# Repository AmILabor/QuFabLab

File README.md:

# QuFabLab

### Open Quantum Experiments for FabLabs and Education

QuFabLab is an open-source platform for building and exploring interactive quantum optics experiments using modular hardware, embedded systems, and augmented reality.

The project combines physical experiment components with real-time AR visualization, allowing students to build optical experiments while simultaneously observing the quantum behavior of the system.

QuFabLab aims to make quantum technologies accessible in FabLabs, universities, and STEM education environments.

---

# Project Overview

QuFabLab is centered around the AR Quantenkoffer (Quantum Suitcase) — a portable experimental platform that enables users to construct optical experiments using modular components.

The system automatically detects the configuration of the experiment and visualizes it using Microsoft HoloLens 2.

This enables a new form of learning where physical experimentation and digital visualization are combined.

---

# System Architecture

```id="g82x1a"
Experiment Bricks
      │
      │  I2C / GPIO
      ▼
Experiment Field
      │
      ▼
Raspberry Pi (QuCase Backend)
      │
      │ WebSocket
      ▼
AR Visualization (HoloLens 2)
```

1. Users place experiment bricks on the experiment field
2. The Raspberry Pi backend detects the configuration
3. The AR application visualizes the optical system

---

# Repository Structure

```id="9afwks"
QuFabLab
│
├── AR-Quantenkoffer
│   │
│   ├── ar_brick_firmware
│   │   Firmware for the experiment bricks
│   │
│   ├── qucase
│   │   Raspberry Pi control software
│   │
│   ├── Platinen
│   │   PCB designs for the hardware
│   │
│   └── stls
│       3D printable mechanical components
│
├── hololens2
│   Augmented reality visualization application
│
└── moodle
    Educational materials and course integration
```

---

# Core Components

## AR Quantenkoffer

A modular hardware system that allows users to build optical experiments using physical experiment blocks.

Features:

* experiment brick detection
* hardware interface for optical components
* power and communication infrastructure
* modular optical components

---

## Experiment Brick Firmware

Firmware running on the experiment bricks.

Responsibilities include:

* detecting brick orientation
* communicating with the backend via I2C
* displaying brick type and configuration
* providing user configuration via rotary encoder

---

## QuCase Backend

The backend software running on a Raspberry Pi.

Responsibilities:

* detecting experiment bricks
* managing experiment configuration
* communicating with the AR visualization system
* providing APIs for external applications

---

## HoloLens AR Visualization

The HoloLens application displays the experiment in augmented reality.

It visualizes components such as:

* mirrors
* beam splitters
* detectors
* photon paths
* interferometers

---

## Moodle Integration

The project includes educational content designed for structured learning environments.

The Moodle integration provides:

* experiment instructions
* theoretical background
* assignments and exercises
* guided learning modules

---

# Example Experiments

The system can be used to demonstrate concepts such as:

* beam splitting
* interferometry
* photon detection
* optical path interference
* quantum optics fundamentals

---

# Educational Goals

QuFabLab aims to:

- make quantum physics accessible through hands-on experiments
- combine physical experimentation with AR visualization
- provide open hardware for STEM education
- support universities, FabLabs, and makerspaces

---

# Target Audience

* universities
* FabLabs / makerspaces
* physics education programs
* STEM outreach initiatives

---

# Development

The project includes multiple development environments:

| Component      | Technology                  |
| -------------- | --------------------------- |
| Firmware       | C++ / PlatformIO            |
| Backend        | Python                      |
| AR Application | Unity / MRTK                |
| Hardware       | PCB + 3D printed components |

---

# Getting Started

Clone the repository:

```id="n8y5dl"
git clone https://github.com/AmILabor/QuFabLab.git
```

Explore the subprojects:

* `AR-Quantenkoffer`
* `hololens2`
* `moodle`

Each directory contains its own documentation.

---

# Contributing

Contributions are welcome.

Possible contributions include:

* hardware improvements
* firmware development
* AR visualization features
* educational content
* documentation

---

# Research & Educational Use

QuFabLab is designed for use in:

* physics laboratory courses
* STEM education programs
* FabLab workshops
* science outreach events

---

# License

See the individual project folders for license details.

---

# Acknowledgements

QuFabLab is an open initiative to bring quantum technologies into accessible learning environments through open hardware, software, and augmented reality.

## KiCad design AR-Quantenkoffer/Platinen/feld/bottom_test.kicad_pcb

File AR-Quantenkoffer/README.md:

# AR Quantenkoffer

The AR Quantenkoffer (Quantum Suitcase) is a modular experiment platform designed to teach physics concepts using physical experiment components combined with augmented reality visualization.

## Installation

## System Overview

The system consists of three main parts:

1. Experiment Field
   - Detects the position of experiment bricks
   - Provides power and communication

2. Experiment "QuBricks" 
   - Represent optical components (mirrors, beam splitters, etc.)
   - Contain a microcontroller and display
   - Communicate with the main system via I2C

3. Control Software
   - Runs on a Raspberry Pi
   - Detects experiment configuration
   - Communicates with the AR application

## Repository Structure
~~~
AR-Quantenkoffer
│
├── ar_brick_firmware
│ Firmware for the experiment bricks
│
├── qucase
│ Python control software running on the main system
│
├── Platinen
│ PCB designs for the hardware
│
└── stls
3D models for mechanical components
~~~

## Hardware Components

### Field
To print the 3D components, we used an Ultimaker S5.
Each field element consists of the follwing componenets:
  - a custom pcb to detect brick position
  - a pcb holder
  - a pcb cover plate, which convers the pcb and holds magnets to hold the QuBricks in place. 

The complete field contains 30 elements configured as 6 elements wide and 5 elements long. Each field element can hold one QuBrick. The STL-file for the pcb holder field is 3x5 elements and needs to be printed twice. The pcb cover plate needs to be printed 30 times (or 30 dived by the how many you can fit on your printer). 
The Raspberry Pi is connected to the field using the also 3D-printed "pi mount".

### QuBricks

The QuBricks consist of:
- The brick bottom, which contain the magnets that hold the QuBricks in place.
- The brick shell 
- The display fixture, which holds the display.

For the Michelson-Interferometer 6 QuBricks are needed.

The non-3D-printed compontents inside the Brick shell are:

- Rotary Encoder Board KY-40 to set the brick type and mirror distance
- the slef-designed board to which the following elements are added:
  - XIAO SAMD21 microcontroller 
  - PCF8574AN GPIO expander
  - DEBO LCD 1.28" Display 
  - pogo pin connectors
  - 3x 10k Resistor

## Software Componenets

### QuBrick Firmware

### qucase (Rapsberry Pi Software)

## Communication Architecture
~~~
Experiment Brick
↓
I2C Communication
↓
Raspberry Pi (qucase)
↓
WebSocket
↓
AR Application (HoloLens)
~~~

## Usage

1. Insert experiment bricks into the experiment field
2. Wait until the brick has booted and its type appears on the display
3. The system detects the brick position and type
4. The configuration is transmitted to the AR application

## License

See individual subprojects for licensing details.

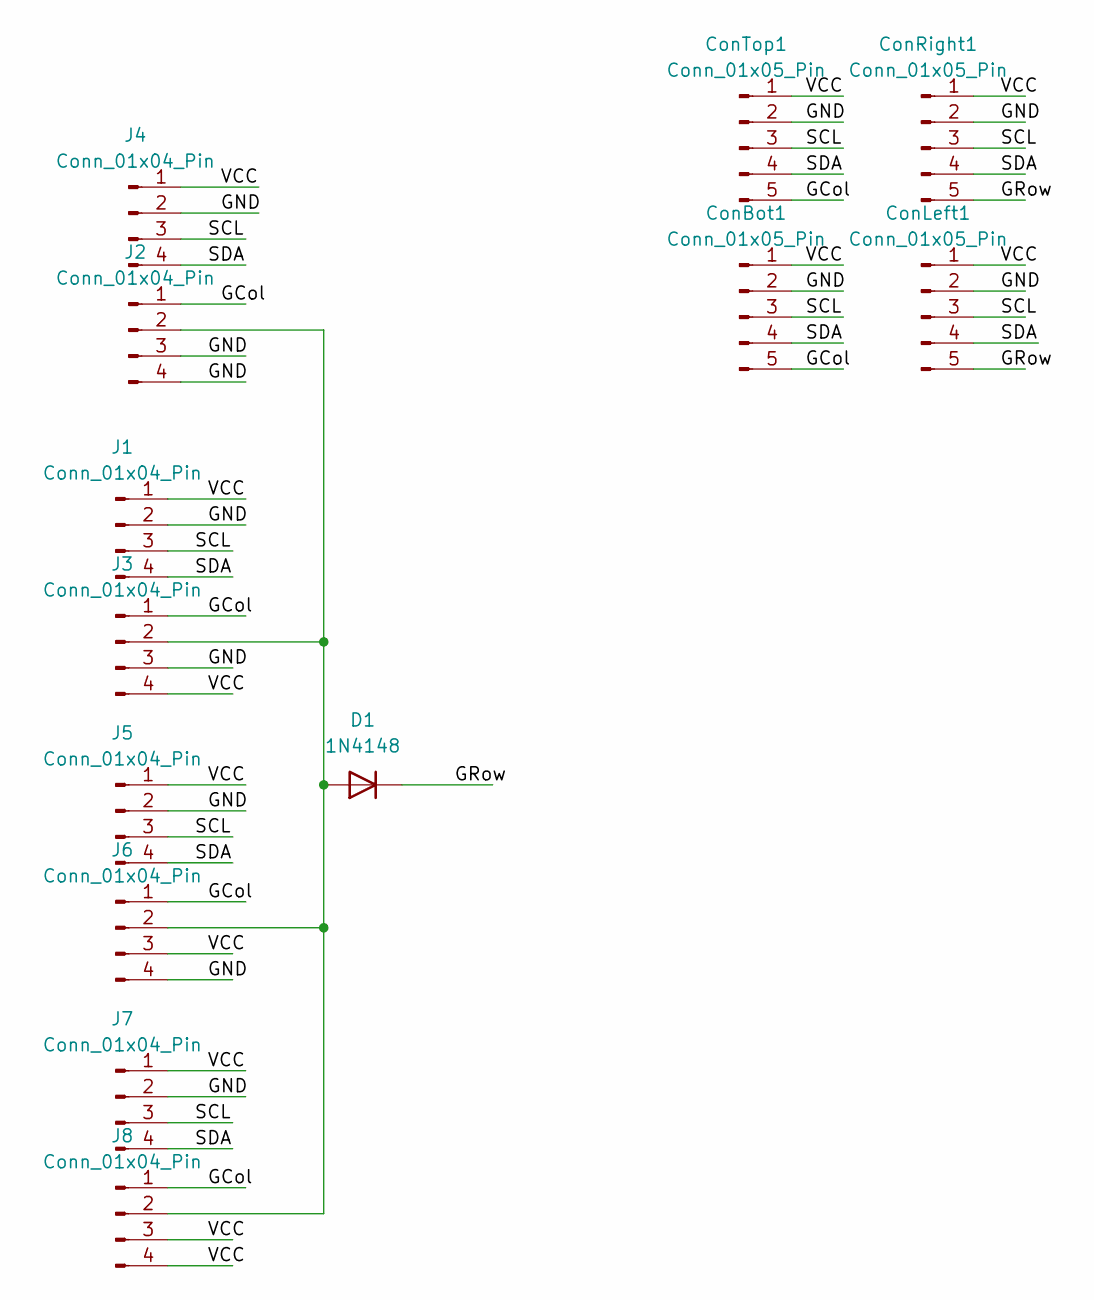
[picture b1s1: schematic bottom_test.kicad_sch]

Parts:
ConBot1: Conn_01x05_Pin; PinSocket_1x05_P2.54mm_Horizontal
ConLeft1: Conn_01x05_Pin; PinHeader_1x05_P2.54mm_Horizontal
ConRight1: Conn_01x05_Pin; PinSocket_1x05_P2.54mm_Horizontal
ConTop1: Conn_01x05_Pin; PinHeader_1x05_P2.54mm_Horizontal
D1: 1N4148; D_DO-35_SOD27_P7.62mm_Horizontal
J1, J2, J3, J4, J5, J6, J7, J8: Conn_01x04_Pin; TestPoint_Pad_01x04_2.54

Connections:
/GCol: ConBot1.5, ConTop1.5, J2.1, J3.1, J6.1, J8.1
/GND: ConBot1.2, ConLeft1.2, ConRight1.2, ConTop1.2, J1.2, J2.3, J2.4, J3.3, J4.2, J5.2, J6.4, J7.2
/GRow: ConLeft1.5, ConRight1.5, D1.1 (K)
/SCL: ConBot1.3, ConLeft1.3, ConRight1.3, ConTop1.3, J1.3, J4.3, J5.3, J7.3
/SDA: ConBot1.4, ConLeft1.4, ConRight1.4, ConTop1.4, J1.4, J4.4, J5.4, J7.4
/VCC: ConBot1.1, ConLeft1.1, ConRight1.1, ConTop1.1, J1.1, J3.4, J4.1, J5.1, J6.3, J7.1, J8.3, J8.4
unnamed: D1.2 (A), J2.2, J3.2, J6.2, J8.2

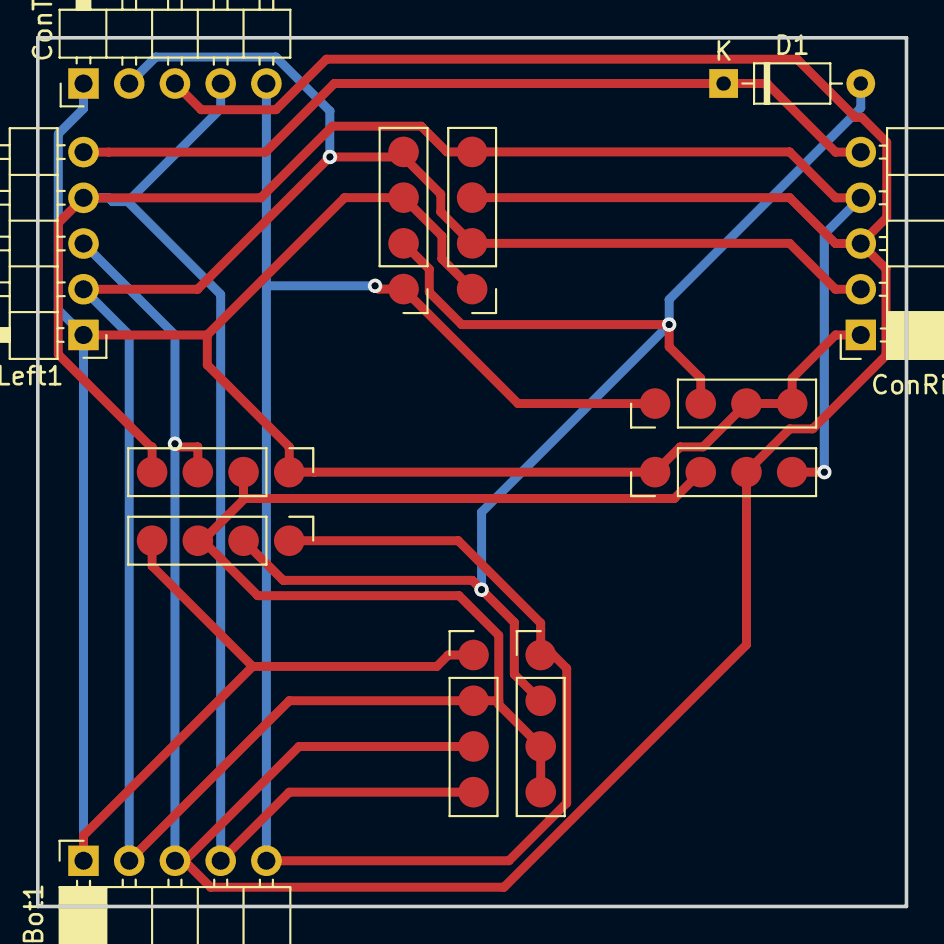
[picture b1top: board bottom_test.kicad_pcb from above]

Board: 2 copper layers, 48.3 x 48.3 mm, 13 parts (0 on the bottom side), 7 nets.

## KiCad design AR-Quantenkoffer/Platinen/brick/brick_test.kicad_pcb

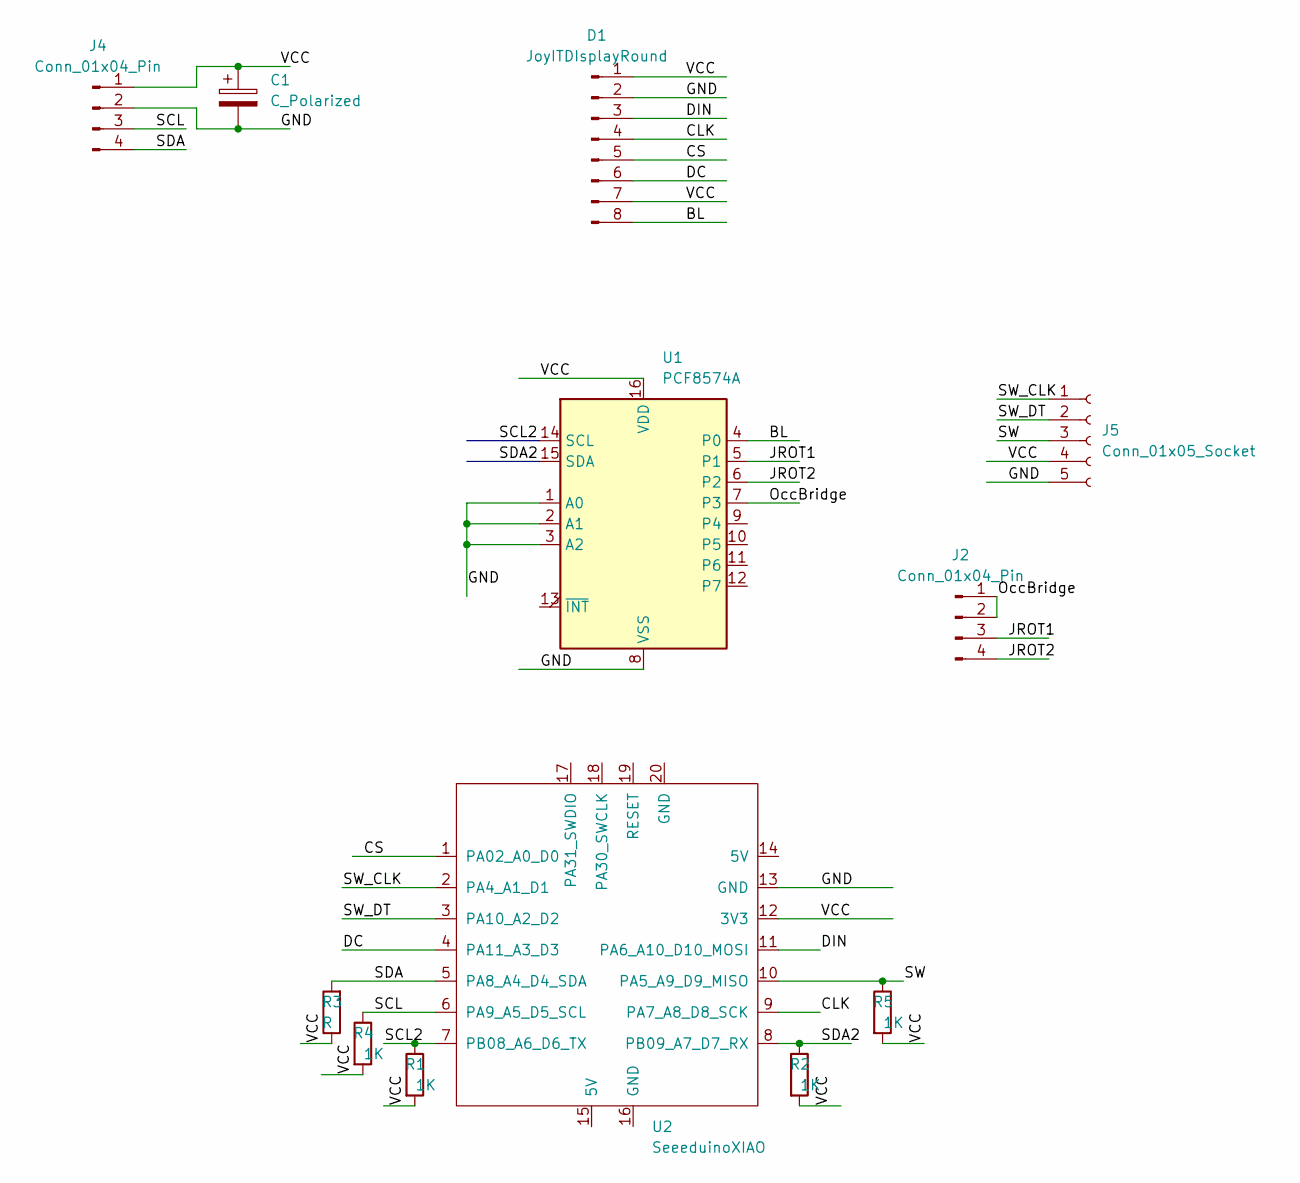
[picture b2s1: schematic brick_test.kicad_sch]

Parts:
C1: C_Polarized; CP_Radial_D8.0mm_P5.00mm
D1: JoyITDIsplayRound; JoyITDisplayRound2
J2, J4: Conn_01x04_Pin; PinHeader_1x04_P2.54mm_Vertical
J5: Conn_01x05_Socket; PinSocket_1x05_P2.54mm_Vertical
R1, R2, R4, R5: 1K; R_Axial_DIN0207_L6.3mm_D2.5mm_P7.62mm_Horizontal
R3: R; R_Axial_DIN0207_L6.3mm_D2.5mm_P7.62mm_Horizontal
U1: PCF8574A; DIP-16_W7.62mm_Socket
U2: SeeeduinoXIAO; MODULE_102010388

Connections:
/BL: D1.8 (BL), U1.4 (P0)
/CLK: D1.4 (CLK), U2.9 (PA7_A8_D8_SCK)
/CS: D1.5 (CS), U2.1 (PA02_A0_D0)
/DC: D1.6 (DC), U2.4 (PA11_A3_D3)
/DIN: D1.3 (DIN), U2.11 (PA6_A10_D10_MOSI)
/GND: C1.2, D1.2 (GND), J4.2, J5.5, U1.1 (A0), U1.2 (A1), U1.3 (A2), U1.8 (VSS), U2.13 (GND)
/JROT1: J2.3, U1.5 (P1)
/JROT2: J2.4, U1.6 (P2)
/OccBridge: J2.1, J2.2, U1.7 (P3)
/SCL: J4.3, R4.1, U2.6 (PA9_A5_D5_SCL)
/SCL2: R1.1, U1.14 (SCL), U2.7 (PB08_A6_D6_TX)
/SDA: J4.4, R3.2, U2.5 (PA8_A4_D4_SDA)
/SDA2: R2.1, U1.15 (SDA), U2.8 (PB09_A7_D7_RX)
/SW: J5.3, R5.1, U2.10 (PA5_A9_D9_MISO)
/SW_CLK: J5.1, U2.2 (PA4_A1_D1)
/SW_DT: J5.2, U2.3 (PA10_A2_D2)
/VCC: C1.1, D1.1 (VCC), D1.7 (RST), J4.1, J5.4, R1.2, R2.2, R3.1, R4.2, R5.2, U1.16 (VDD), U2.12 (3V3)

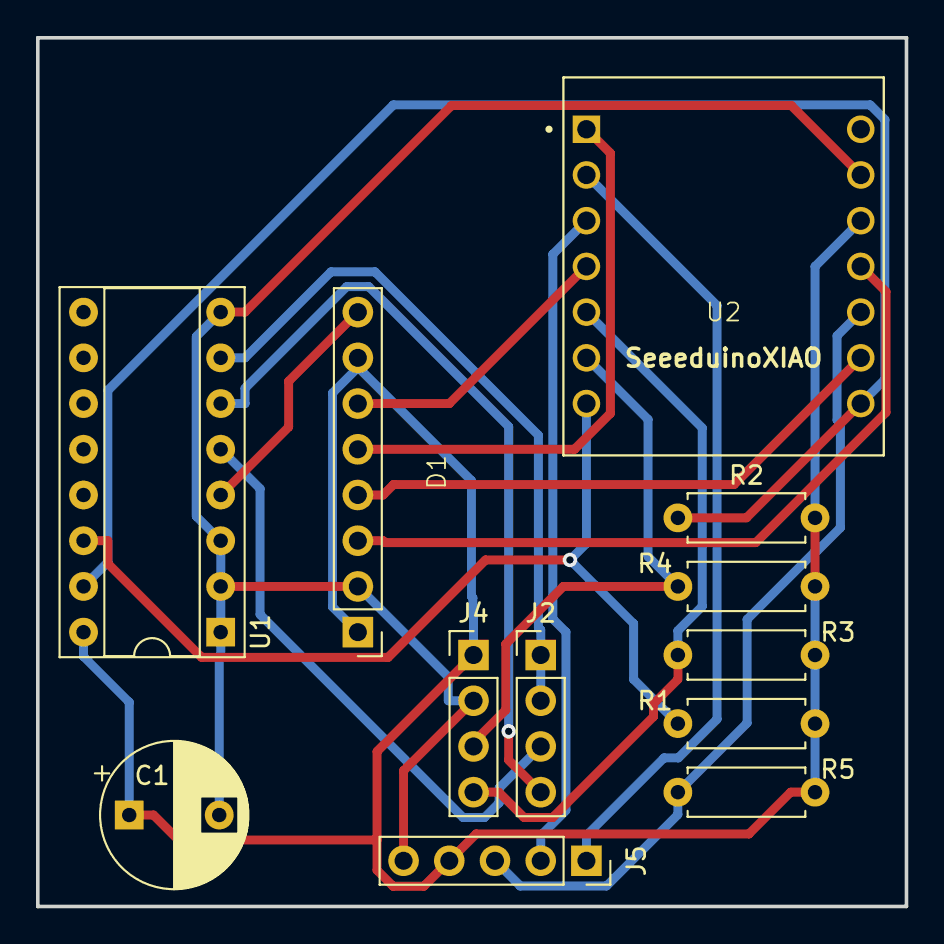
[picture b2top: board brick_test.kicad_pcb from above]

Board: 2 copper layers, 48.3 x 48.3 mm, 12 parts (0 on the bottom side), 17 nets.

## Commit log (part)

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2026-02-26 Upload AR Board stl files
2026-02-26 Upload circuit board files
2026-03-09 Upload Moodle Docker
2026-03-09 Upload AR/VR Code
2026-03-10 Commit Qucase and Brick Software
2026-03-10 Added READMEs
2026-03-16 Update hololens Readme
2026-05-06 Updated ar_brick_firmware with functions for status LEDs
2026-06-26 Update LED logic
